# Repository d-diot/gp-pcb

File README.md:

# d-diot General Purpose Pcb for Arduino Pro Mini

This pcb is part of the [d-diot project](https://www.d-diot.com).

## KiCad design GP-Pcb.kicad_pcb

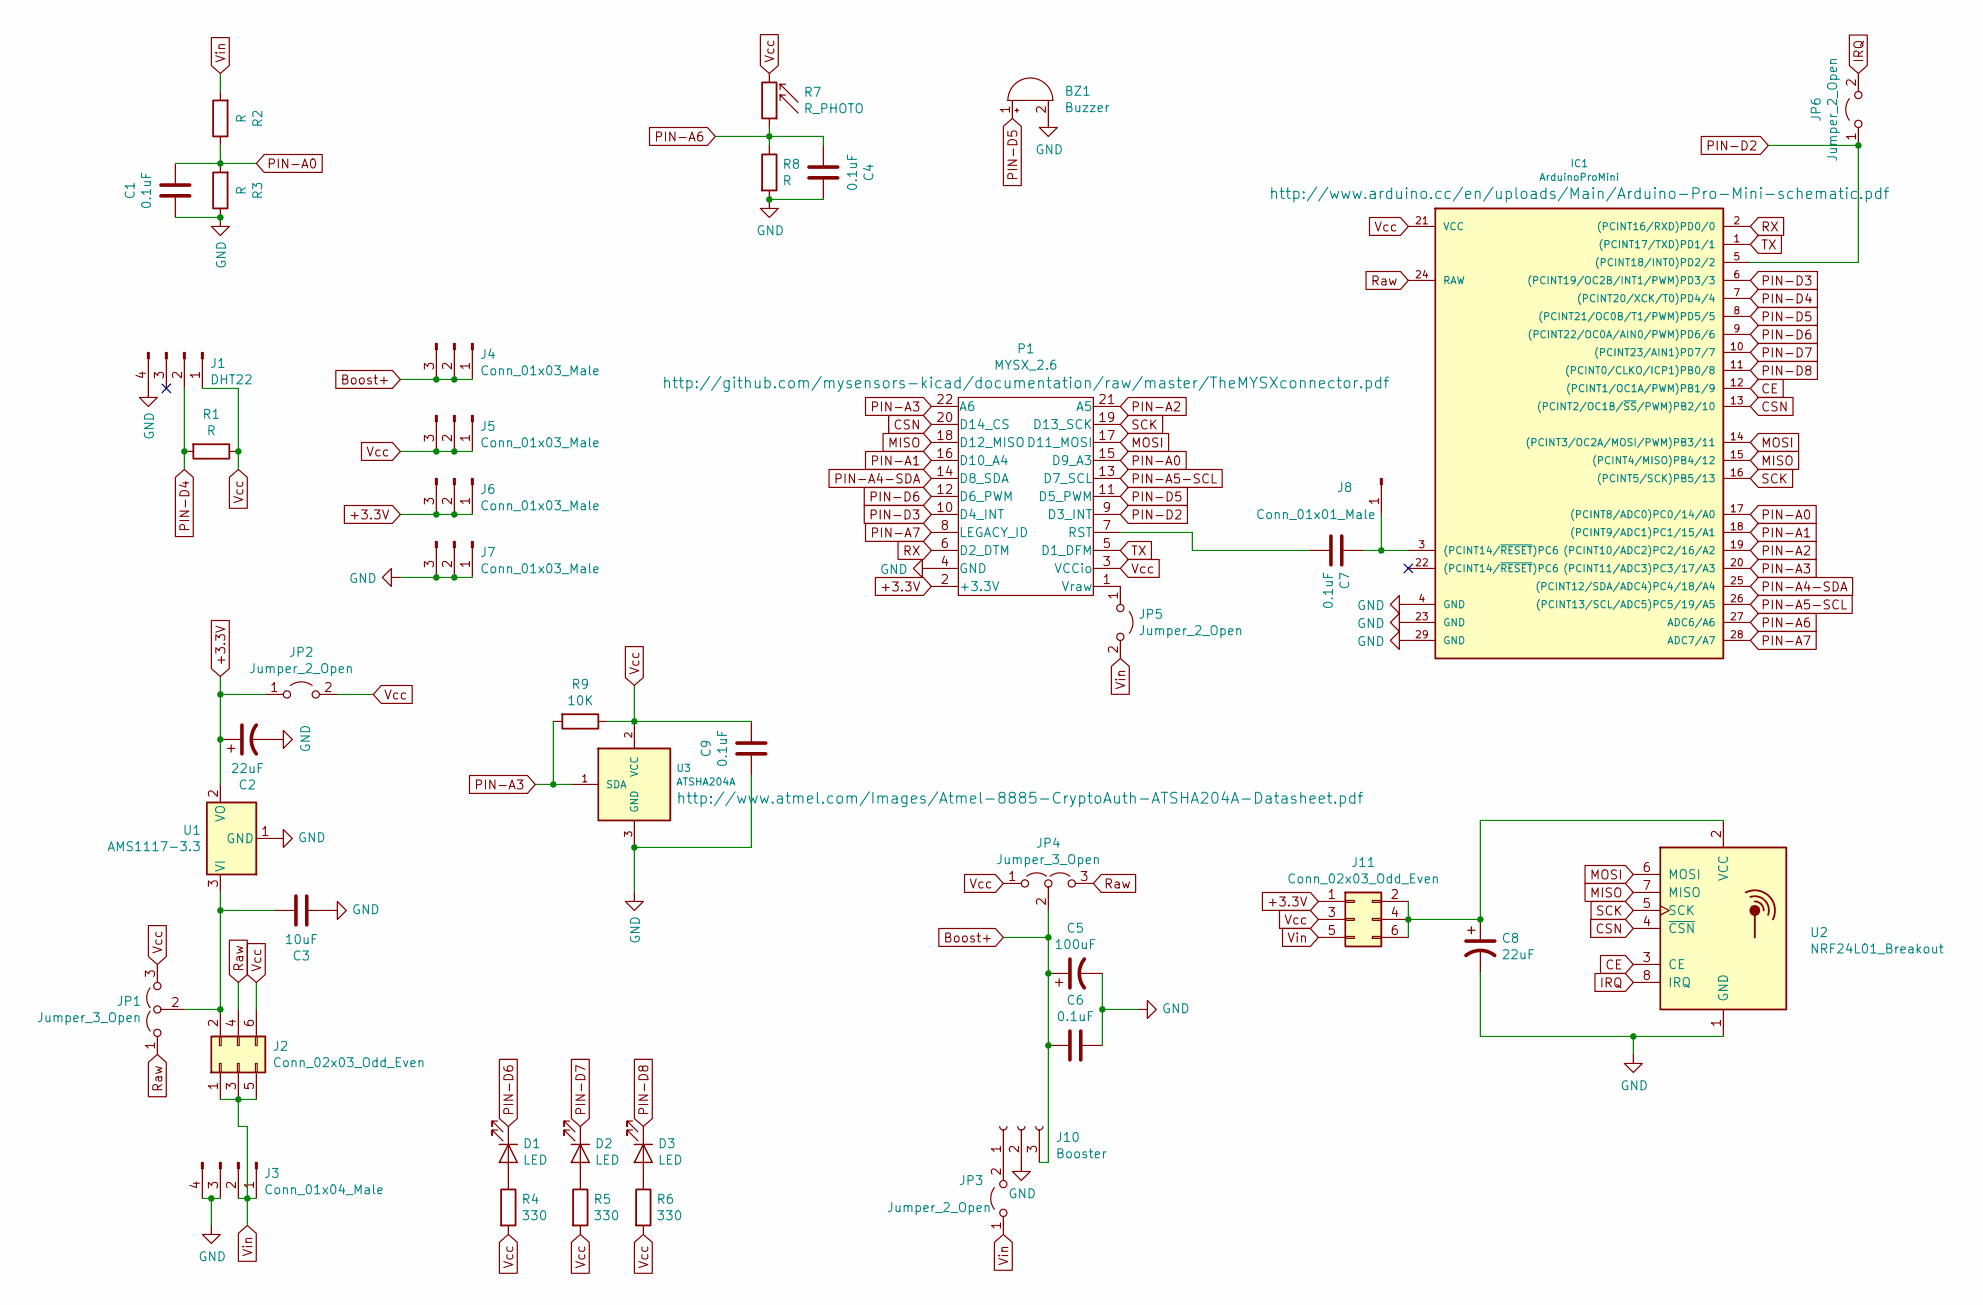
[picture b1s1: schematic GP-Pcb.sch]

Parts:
BZ1: Buzzer; Buzzer_12x9.5RM7.6
C1, C4, C6, C7, C9: 0.1uF; C_Disc_D5.1mm_W3.2mm_P5.00mm
C2: 22uF; CP_Radial_Tantal_D5.5mm_P2.50mm
C3: 10uF; C_Disc_D5.1mm_W3.2mm_P5.00mm
C5: 100uF; CP_Radial_D6.3mm_P2.50mm
C8: 22uF; CP_Radial_D5.0mm_P2.00mm
D1, D2, D3: LED; LED_D5.0mm
IC1: ArduinoProMini; pro_mini
J1: DHT22; PinHeader_1x04_P2.54mm_Vertical
J2, J11: Conn_02x03_Odd_Even; PinHeader_2x03_P2.54mm_Vertical
J3: Conn_01x04_Male; PinHeader_1x04_P2.54mm_Vertical
J4, J5, J6, J7: Conn_01x03_Male; PinHeader_1x03_P2.54mm_Vertical
J8: Conn_01x01_Male; PinHeader_1x01_P2.54mm_Vertical
J10: Booster; PinHeader_1x03_P2.54mm_Vertical
JP1, JP4: Jumper_3_Open; PinHeader_1x03_P2.54mm_Vertical
JP2, JP3, JP5, JP6: Jumper_2_Open; PinHeader_1x02_P2.54mm_Vertical
P1: MYSX_2.6; MYSX_2.6_SOCKET
R1, R2, R3, R8: R; R_Axial_DIN0207_L6.3mm_D2.5mm_P7.62mm_Horizontal
R4, R5, R6: 330; R_Axial_DIN0207_L6.3mm_D2.5mm_P7.62mm_Horizontal
R7: R_PHOTO; R_LDR_5.0x4.1mm_P3mm_Vertical
R9: 10K; R_Axial_DIN0207_L6.3mm_D2.5mm_P7.62mm_Horizontal
U1: AMS1117-3.3; SOT-223-3_TabPin2
U2: NRF24L01_Breakout; nRF24L01_Breakout
U3: ATSHA204A; SOT-23_Handsoldering

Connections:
+3.3V: C2.1, J6.1, J6.2, J6.3, J11.1, JP2.1 (A), P1.2 (+3.3V), U1.2 (VO)
Boost+: C5.1, C6.2, J4.1, J4.2, J4.3, J10.3, JP4.2 (C)
CE: IC1.12 ((PCINT1/OC1A/PWM)PB1/9), U2.3 (CE)
CSN: IC1.13 ((PCINT2/OC1B/~SS~/PWM)PB2/10), P1.20 (D14_CS), U2.4 (~CSN)
GND: BZ1.2 (+), C1.1, C2.2, C3.2, C4.2, C5.2, C6.1, C8.2, C9.1, IC1.4 (GND), IC1.23 (GND), IC1.29 (GND), J1.4, J3.3, J3.4, J7.1, J7.2, J7.3, J10.2, P1.4 (GND), R3.1, R8.2, U1.1 (GND), U2.1 (GND), U3.3 (GND)
IRQ: JP6.2 (B), U2.8 (IRQ)
MISO: IC1.15 ((PCINT4/MISO)PB4/12), P1.18 (D12_MISO), U2.7 (MISO)
MOSI: IC1.14 ((PCINT3/OC2A/MOSI/PWM)PB3/11), P1.17 (D11_MOSI), U2.6 (MOSI)
unnamed: C3.1, J2.2, JP1.2 (C), U1.3 (VI)
unnamed: C7.1, P1.7 (RST)
unnamed: C7.2, IC1.3 ((PCINT14/~RESET~)PC6), J8.1
unnamed: C8.1, J11.2, J11.4, J11.6, U2.2 (VCC)
unnamed: D1.2 (A), R4.1
unnamed: D2.2 (A), R5.1
unnamed: D3.2 (A), R6.1
unnamed: J10.1, JP3.2 (B)
unnamed: JP5.1 (A), P1.1 (Vraw)
PIN-A0: C1.2, IC1.17 ((PCINT8/ADC0)PC0/14/A0), P1.15 (D9_A3), R2.1, R3.2
PIN-A1: IC1.18 ((PCINT9/ADC1)PC1/15/A1), P1.16 (D10_A4)
PIN-A2: IC1.19 ((PCINT10/ADC2)PC2/16/A2), P1.21 (A5)
PIN-A3: IC1.20 ((PCINT11/ADC3)PC3/17/A3), P1.22 (A6), R9.2, U3.1 (SDA)
PIN-A4-SDA: IC1.25 ((PCINT12/SDA/ADC4)PC4/18/A4), P1.14 (D8_SDA)
PIN-A5-SCL: IC1.26 ((PCINT13/SCL/ADC5)PC5/19/A5), P1.13 (D7_SCL)
PIN-A6: C4.1, IC1.27 (ADC6/A6), R7.1, R8.1
PIN-A7: IC1.28 (ADC7/A7), P1.8 (LEGACY_ID)
PIN-D2: IC1.5 ((PCINT18/INT0)PD2/2), JP6.1 (A), P1.9 (D3_INT)
PIN-D3: IC1.6 ((PCINT19/OC2B/INT1/PWM)PD3/3), P1.10 (D4_INT)
PIN-D4: IC1.7 ((PCINT20/XCK/T0)PD4/4), J1.2, R1.2
PIN-D5: BZ1.1 (-), IC1.8 ((PCINT21/OC0B/T1/PWM)PD5/5), P1.11 (D5_PWM)
PIN-D6: D1.1 (K), IC1.9 ((PCINT22/OC0A/AIN0/PWM)PD6/6), P1.12 (D6_PWM)
PIN-D7: D2.1 (K), IC1.10 ((PCINT23/AIN1)PD7/7)
PIN-D8: D3.1 (K), IC1.11 ((PCINT0/CLKO/ICP1)PB0/8)
RX: IC1.2 ((PCINT16/RXD)PD0/0), P1.6 (D2_DTM)
Raw: IC1.24 (RAW), J2.4, JP1.1 (A), JP4.3 (B)
SCK: IC1.16 ((PCINT5/SCK)PB5/13), P1.19 (D13_SCK), U2.5 (SCK)
TX: IC1.1 ((PCINT17/TXD)PD1/1), P1.5 (D1_DFM)
Vcc: C9.2, IC1.21 (VCC), J1.1, J2.6, J5.1, J5.2, J5.3, J11.3, JP1.3 (B), JP2.2 (B), JP4.1 (A), P1.3 (VCCio), R1.1, R4.2, R5.2, R6.2, R7.2, R9.1, U3.2 (VCC)
Vin: J2.1, J2.3, J2.5, J3.1, J3.2, J11.5, JP3.1 (A), JP5.2 (B), R2.2

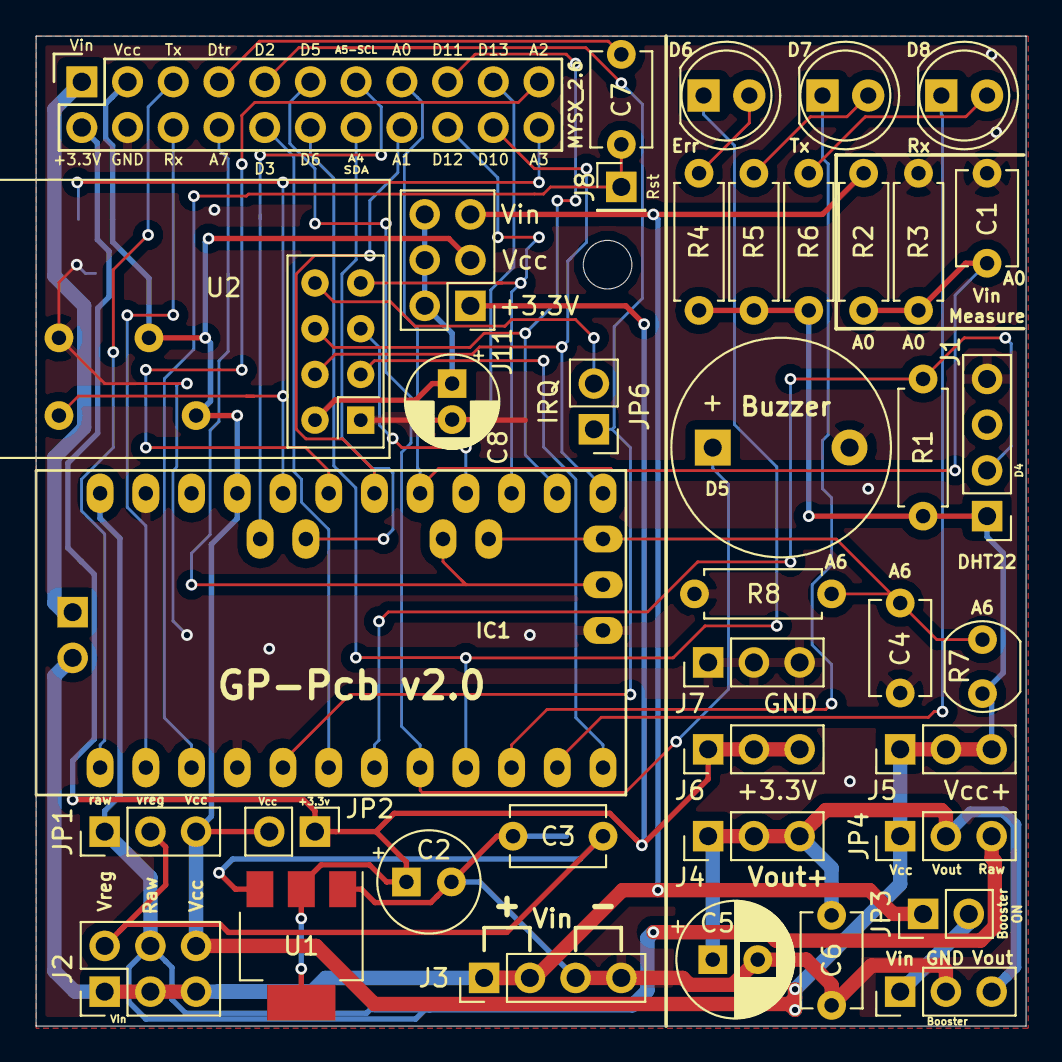
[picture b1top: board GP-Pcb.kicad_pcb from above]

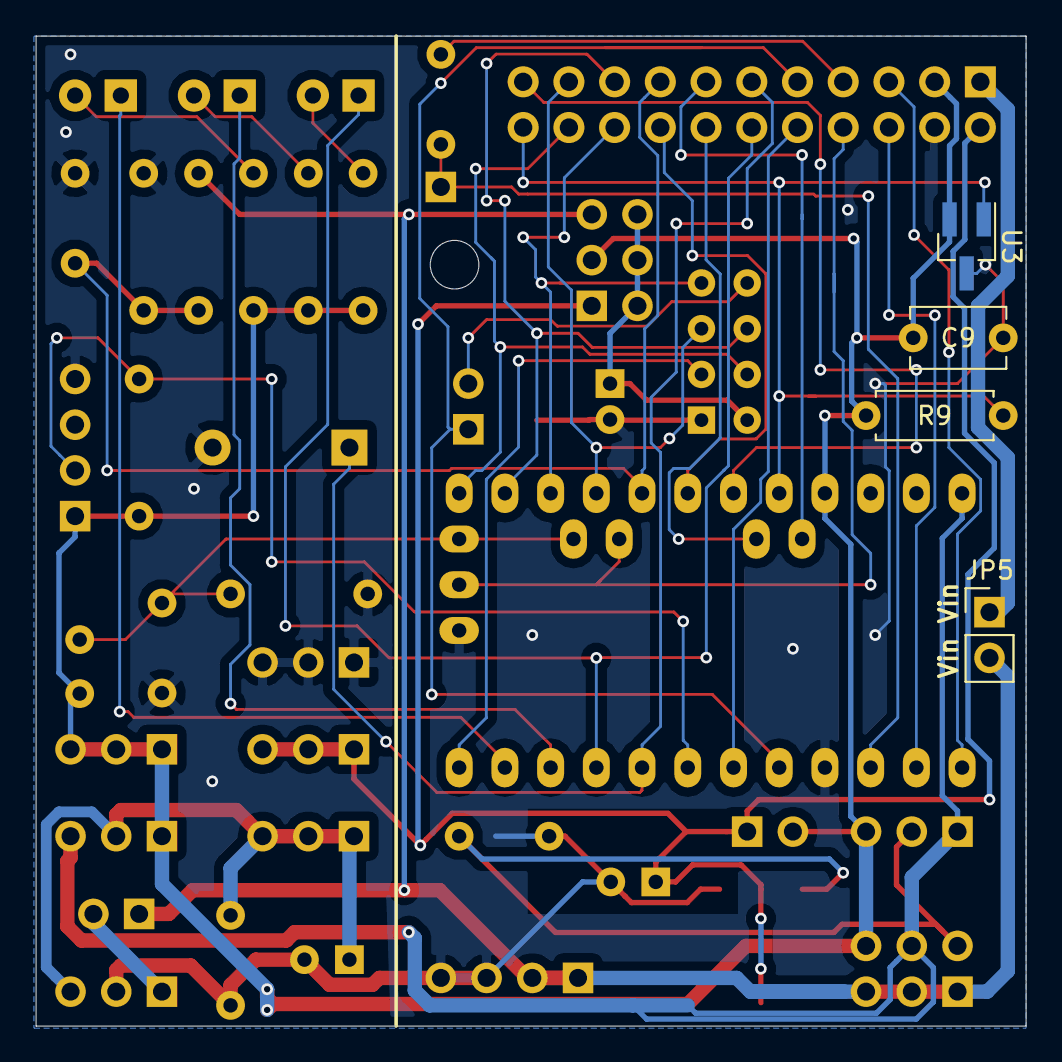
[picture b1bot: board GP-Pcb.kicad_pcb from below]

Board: 2 copper layers, 55.0 x 55.0 mm, 43 parts (5 on the bottom side), 38 nets.

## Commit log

2019-06-30 GP Pcb v.2.0
